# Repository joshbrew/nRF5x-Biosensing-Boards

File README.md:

# nRF52/53 Biosensing Boards

This contains our working prototypes for using nRF52 and nRF53 microcontrollers (ARM + BLE5) with low cost sensors. [Doc](https://docs.google.com/document/d/1gOrWiBDynYziCYDMF4r1Rw85PXo9JbuBrYJEEkW2U-c/edit?usp=sharing). 

License: AGPL v3.0 copyleft (public domain). You may do whatever you want with our designs, but you are obligated to share your modifications and advancements publicly. This is in hopes of facilitating a better community around useful wearable medical hardware designs.

The current prototypes here are working breakout boards. They are pin compatible with several different modules while it's easy to spin up new designs with similar products by Fanstel.

Features Zephyr RTOS test firmware, which is hardware-agnostic. 

### Designs included

- BT40/BT840, pin compatible with any Fanstel BT-series but mind the pinouts as not all will work without modification, but most should.
- BC840M
- BC40M
- BT832A (do not use, this was our first attempt)

### Firmware included

- nRF5340
- nRF52840
- nRF52810 (for the BT832A prototype)

### Sensor Support 
- ADS131M08 (8 channel sigma delta converter), there is one on-board 
- MPU6050 accelerometer
- QMC5883L magnetometer (for 9-axis movement when combined with MPU6050)
- MAX30102 pulse oximeter, 
- BMP/BME280 environmental sensor, 
- Additional 8 channel ADS131M08 for up to 16 raw data channels, each individually configurable. 
- MAX98357A Audio output amplifier
- B079Q8G7N1 PDM MEMS microphone

### [Driver Docs](https://docs.google.com/document/d/1eThhvpdm9zZMaKTB0dwuHXi1aBz_5ESBecHRZPxs0kE/edit?usp=sharing)

You can fairly easily add more sensor modules, which are all plug-and-play so the board can run with any combination of sensors. We'll clean this up more as we go for easier customization and feature inclusions. The BT840/BT40, BC840M, and BC40M prototypes include battery chargers with TVS diodes for safety so the boards could be FDA-approved.

Version 3 (BT40/BT840, BC840M R2 & BC40M R1 designs) by Joshua Brewster and Bojan Jovanovich. Firmware by Bojan Jovanovich, drawings and frontend software by Josh Brewster. 

Versions 2 (BC840M R1) by Joshua Brewster, Jacob Tinkhauser, Bojan Jovanovich. Firmware by Bojan, drawings and frontend software by Josh Brewster. Testing and early design phase included Jacob Tinkhauser. 

Version 0 (BT832A) by Joshua Brewster, Jacob Tinkhauser, and Bojan Jovanovich. Firmware by Bojan and Jacob, drawings and frontend by Joshua Brewster.

Developed for creating open source wearables for biofeedback and treatment recovery monitoring.

Related:
- [BLE & USB Web drivers and debugger](https://github.com/joshbrew/device_debugger)

Below results with the ADS131M08 doing quick tests. Noise floor was around 350 nanovolts when shorted. These are not final results but show lots of promise.

- EEG alpha waves (spikes are blinks through a digital bandpass filter)

- ECG with additional digital 50Hz lowpass

- Raw EOG

- Raw PPG wave (red LED + Photodiode BPW 34 w/ basic 1MOhm + 200pf lowpass filter)

Note the ADS131M08 is pretty much completely useless on USB power as we do not have digital or power isolators. We recommend sticking with the Bluetooth 5 and battery support except for when debugging.

Todos:
- PDFs, but the free EAGLE version works for these simple boards.
- Make the firmware more API-like for adding sensors and easier to cross-compile.
- Upgrade zephyr firmware version to latest Nordic SDK version, need to redo dependencies.
- Finish NFC integration
- Fine tune data throttling

Bug fixing notes:
- Bojan note (old, worked elsewhere): Sensors not booting, build error with the audio settings

Exploratory:
- SD card
- Integration with a graphical device (stay tuned :-))
- Vibration motor integration (just a GPIO on/off)
- Frontend controls for the whole command interface in javascript
- GPS (e.g. LG77L)
- More design modularity, e.g. attachments and hubs

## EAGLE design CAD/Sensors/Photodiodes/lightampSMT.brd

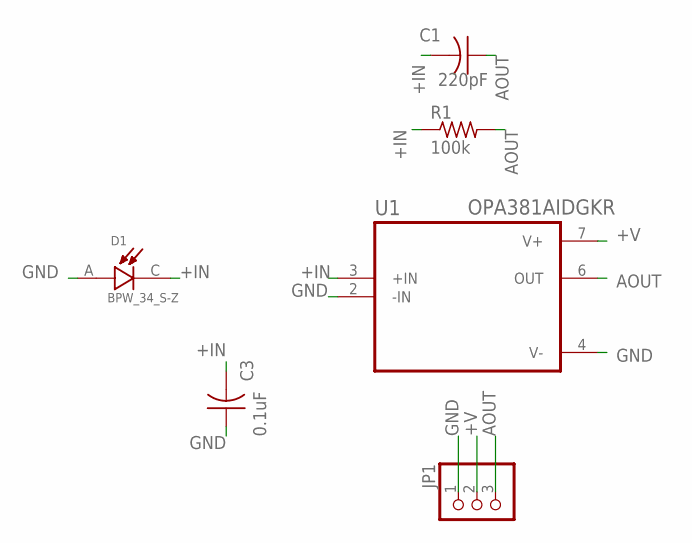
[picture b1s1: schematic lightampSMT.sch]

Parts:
C1: 220pF; C0603K
C3: 0.1uF; C0603K
D1: BPW_34_S-Z; DIO_BPW_34_S-Z
JP1: PINHD-1X3; 1X03
R1: 100k; R0603
U1: OPA381AIDGKR; SOP65P490X110-8N

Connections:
+IN: C1.2, C3.2, D1.C, R1.1, U1.3 (+IN)
+V: JP1.2, U1.7 (V+)
AOUT: C1.1, JP1.3, R1.2, U1.6 (OUT)
GND: C3.1, D1.A, JP1.1, U1.2 (-IN), U1.4 (V-)

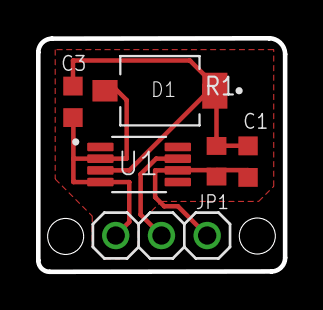
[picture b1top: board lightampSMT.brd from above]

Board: 2 copper layers, 13.7 x 13.0 mm, 6 parts (0 on the bottom side), 4 nets.

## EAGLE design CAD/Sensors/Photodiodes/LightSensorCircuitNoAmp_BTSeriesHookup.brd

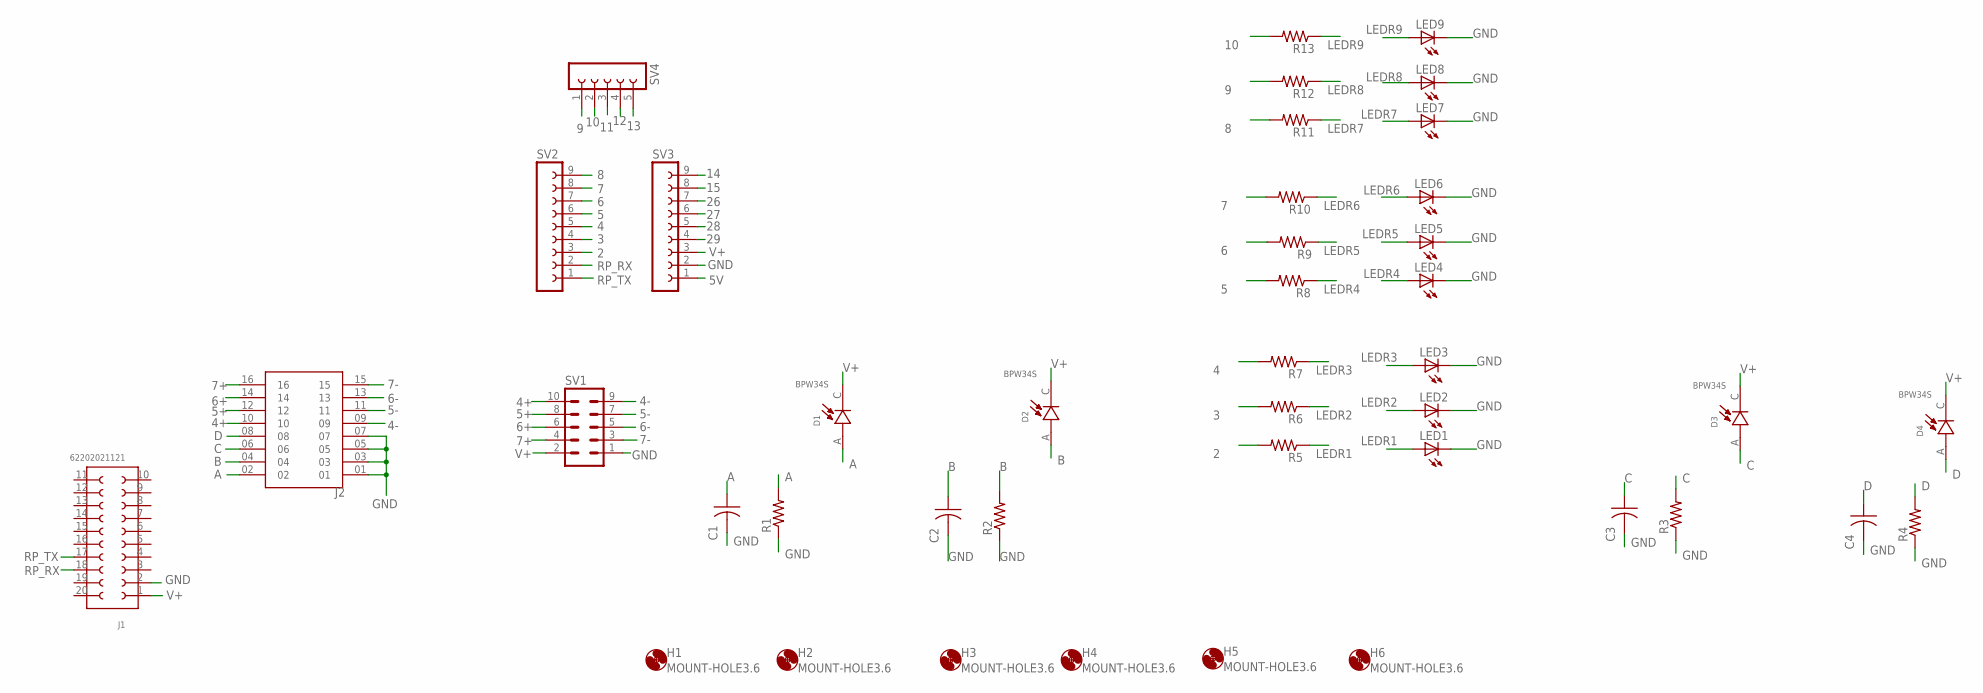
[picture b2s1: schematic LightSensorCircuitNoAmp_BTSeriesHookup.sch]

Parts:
C1, C2, C3, C4: C-US025-025X050; C025-025X050
D1, D2, D3, D4: BPW34S; DIO_BPW34S
H1, H2, H3, H4, H5, H6: MOUNT-HOLE3.6; 3,6
J1: 62202021121
J2: FTSH-108-02-LM-D-ES; SAMTEC_FTSH-108-02-LM-D-ES
LED1, LED2, LED3, LED4, LED5, LED6, LED7, LED8, LED9: LEDCHIPLED_1206; CHIPLED_1206
R1, R2, R3, R4, R5, R6, R7, R8, R9, R10, R11, R12, R13: R-US_0204/5; 0204/5
SV1: MA05-2
SV2, SV3: FE09-1; FE09
SV4: FE05-1

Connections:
2: R5.2, SV2.3
3: R6.2, SV2.4
4: R7.2, SV2.5
4+: J2.10, SV1.10
4-: J2.09, SV1.9
5: R8.2, SV2.6
5+: J2.12, SV1.8
5-: J2.11, SV1.7
5V: SV3.1
6: R9.2, SV2.7
6+: J2.14, SV1.6
6-: J2.13, SV1.5
7: R10.2, SV2.8
7+: J2.16, SV1.4
7-: J2.15, SV1.3
8: R11.2, SV2.9
9: R12.2, SV4.1
10: R13.2, SV4.2
11: SV4.3
12: SV4.4
13: SV4.5
14: SV3.9
15: SV3.8
26: SV3.7
27: SV3.6
28: SV3.5
29: SV3.4
A: C1.1, D1.A, J2.02, R1.2
B: C2.1, D2.A, J2.04, R2.2
C: C3.1, D3.A, J2.06, R3.2
D: C4.1, D4.A, J2.08, R4.2
GND: C1.2, C2.2, C3.2, C4.2, J1.2, J2.01, J2.03, J2.05, J2.07, LED1.C, LED2.C, LED3.C, LED4.C, LED5.C, LED6.C, LED7.C, LED8.C, LED9.C, R1.1, R2.1, R3.1, R4.1, SV1.1, SV3.2
LEDR1: LED1.A, R5.1
LEDR2: LED2.A, R6.1
LEDR3: LED3.A, R7.1
LEDR4: LED4.A, R8.1
LEDR5: LED5.A, R9.1
LEDR6: LED6.A, R10.1
LEDR7: LED7.A, R11.1
LEDR8: LED8.A, R12.1
LEDR9: LED9.A, R13.1
RP_RX: J1.18, SV2.2
RP_TX: J1.17, SV2.1
V+: D1.C, D2.C, D3.C, D4.C, J1.1, SV1.2, SV3.3

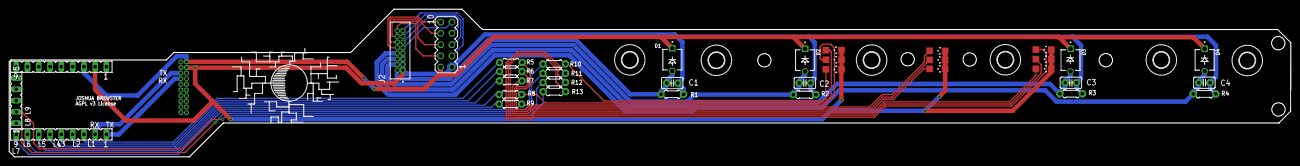
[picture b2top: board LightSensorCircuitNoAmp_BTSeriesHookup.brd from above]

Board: 2 copper layers, 288.6 x 33.2 mm, 42 parts (1 on the bottom side), 34 nets.

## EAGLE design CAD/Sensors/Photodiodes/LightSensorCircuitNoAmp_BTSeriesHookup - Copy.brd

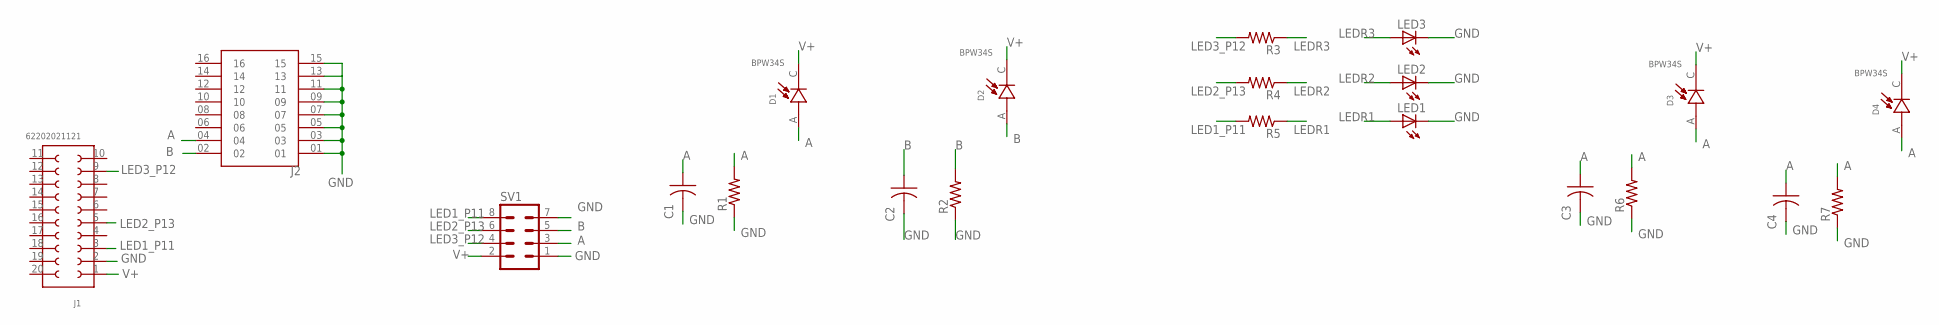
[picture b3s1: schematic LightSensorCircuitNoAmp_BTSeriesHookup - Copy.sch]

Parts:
C1, C2, C3, C4: C-US025-025X050; C025-025X050
D1, D2, D3, D4: BPW34S; DIO_BPW34S
J1: 62202021121
J2: FTSH-108-02-LM-D-ES; SAMTEC_FTSH-108-02-LM-D-ES
LED1, LED2, LED3: LEDCHIPLED_1206; CHIPLED_1206
R1, R2, R3, R4, R5, R6, R7: R-US_0204/5; 0204/5
SV1: MA04-2

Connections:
A: C1.1, C3.1, C4.1, D1.A, D3.A, D4.A, J2.04, R1.2, R6.2, R7.2, SV1.3
B: C2.1, D2.A, J2.02, R2.2, SV1.5
GND: C1.2, C2.2, C3.2, C4.2, J1.2, J2.01, J2.03, J2.05, J2.07, J2.09, J2.11, J2.13, J2.15, LED1.C, LED2.C, LED3.C, R1.1, R2.1, R6.1, R7.1, SV1.1, SV1.7
LED1_P11: J1.3, R5.2, SV1.8
LED2_P13: J1.5, R4.2, SV1.6
LED3_P12: J1.9, R3.2, SV1.4
LEDR1: LED1.A, R5.1
LEDR2: LED2.A, R4.1
LEDR3: LED3.A, R3.1
V+: D1.C, D2.C, D3.C, D4.C, J1.1, SV1.2

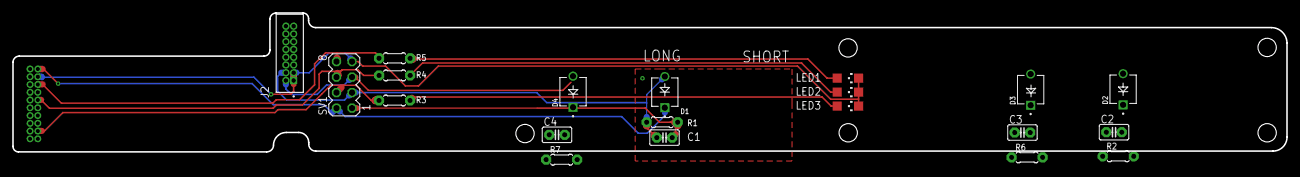
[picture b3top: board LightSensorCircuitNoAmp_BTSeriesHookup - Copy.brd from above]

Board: 2 copper layers, 208.6 x 22.7 mm, 21 parts (1 on the bottom side), 10 nets.

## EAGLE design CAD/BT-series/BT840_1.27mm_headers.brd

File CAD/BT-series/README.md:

Designed for BT840 but compatibile with all Fanstel BT-series microcontrollers (incl BT40 minus the single extra GPIO)

Low cost, minimal size, all 6 mil traces.

Refer to datasheet for BT40 pinout, the board is configured for the BT840 which also has one less pin:

https://www.mouser.com/datasheet/2/915/Fanstel_08262021_BT40F_Product_Specificationsv1_01-2530184.pdf

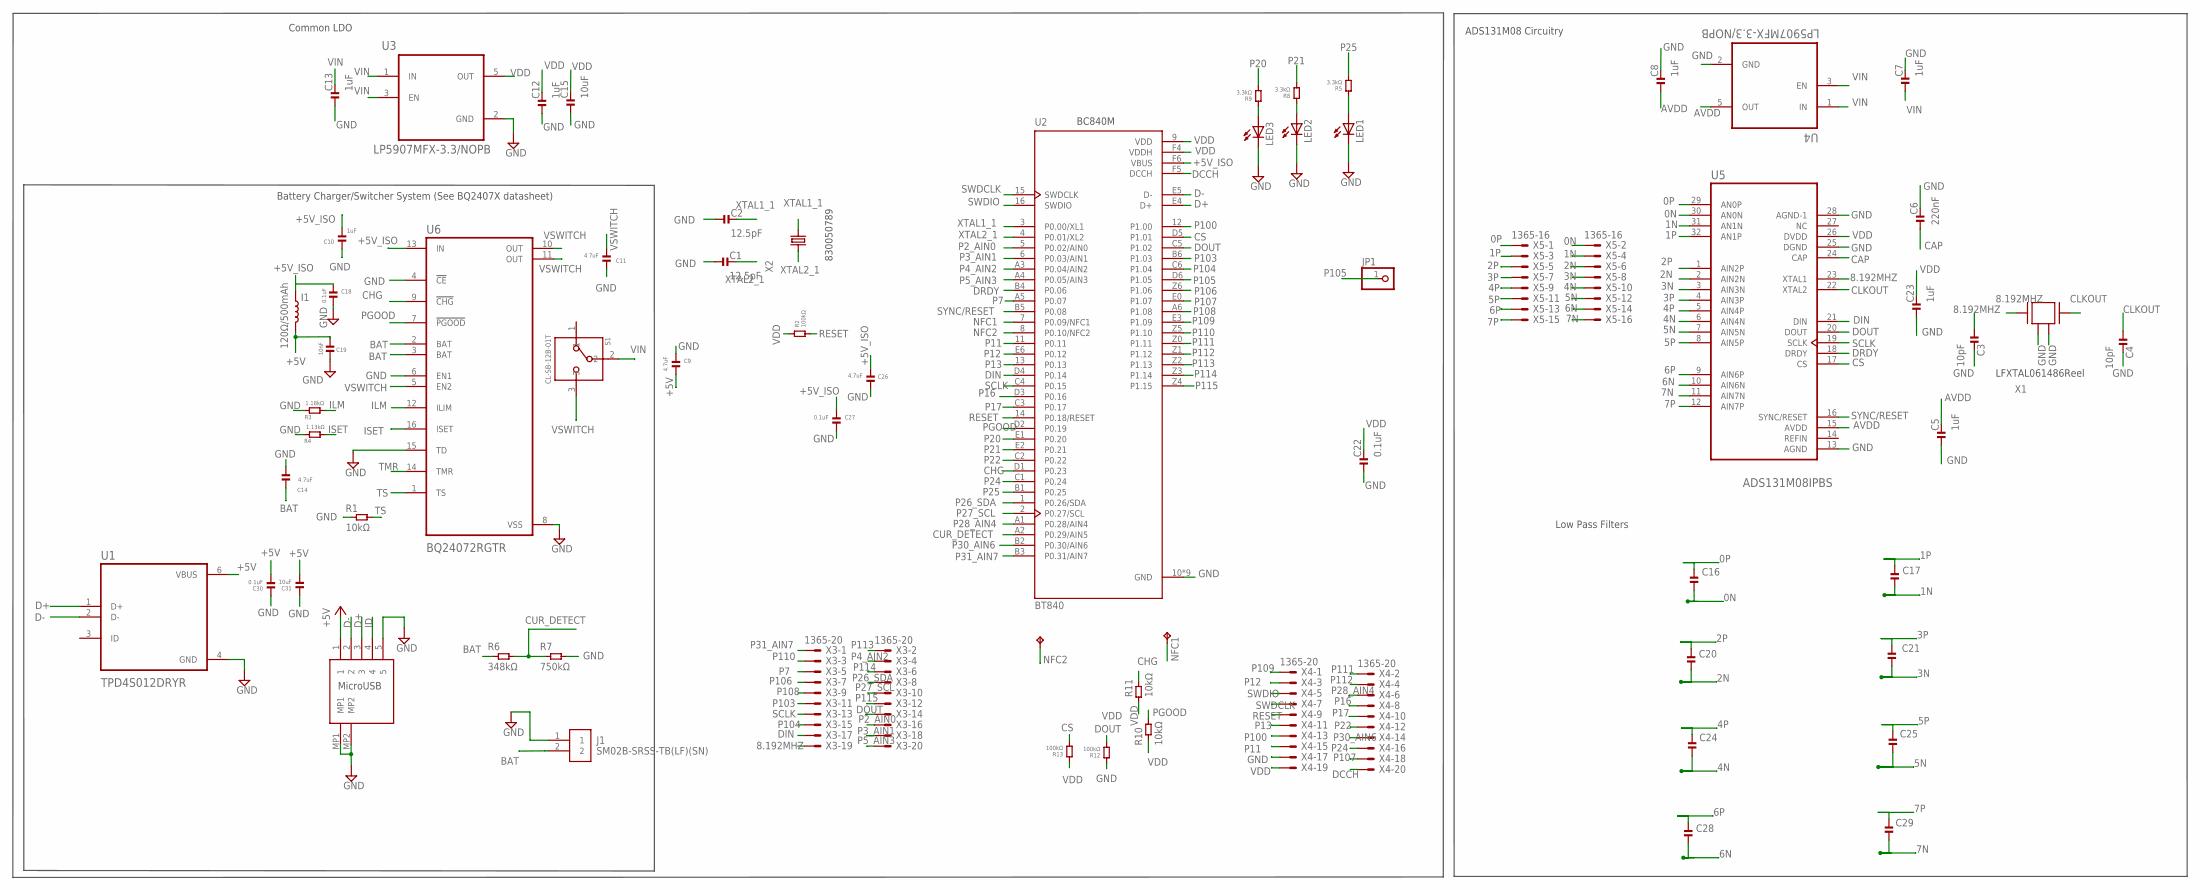
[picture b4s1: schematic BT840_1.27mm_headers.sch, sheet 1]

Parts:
C1, C2: 12.5pF; 0201
C3, C4: 10pF; 0201
C5, C7, C8, C10, C12, C13, C23: 1uF; 0201
C6: 220nF; 0201
C9, C11, C14, C26: 4.7uF; 0201
C15, C31: 10uF; 0402
C16, C17, C20, C21, C24, C25, C28, C29: 100pF; 0201
C18, C22, C27, C30: 0.1uF; 0201
C19: 10nF; 0201
I1: 120Ω/500mAh; 0402_COILCRAFT
J1: SM02B-SRSS-TB(LF)(SN)
JP1: PINHD-1X1; 1X01
LED1, LED2, LED3: LEDCHIPLED_0603; CHIPLED_0603
NFC1, NFC2: TPTP14SQ; TP14SQ
R1: 10kΩ; 0201
R2: 100kΩ; 0201
R3: 1.18kΩ; 0201
R4: 1.13kΩ; 0201
R5, R8, R9: 3.3kΩ; 0201
R6: 348kΩ; 0201
R7: 750kΩ; 0201
R10, R11: 10kΩ; 0402
R12, R13: 100kΩ; 0402
S1: CL-SB-12B-01T; CL-SB-12B
U1: TPD4S012DRYR; PSON50P145X100X60-6N
U2: BT840; XCVR_BT840
U3, U4: LP5907MFX-3.3/NOPB; SOT95P280X145-5N
U5: ADS131M08IPBS; QFP50P700X700X120-32N
U6: BQ24072RGTR; QFN50P300X300X100-17N
U7: DX4R005JJ2R1800
X1: ABM3B-8.000MHZ-B2-T
X2: FC-12M
X3, X4: 1365-20
X5: 1365-16

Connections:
0N: C16.2, U5.30 (AN0N), X5.2
0P: C16.1, U5.29 (AN0P), X5.1
1N: C17.2, U5.31 (AN1N), X5.4
1P: C17.1, U5.32 (AN1P), X5.3
2N: C20.2, U5.2 (AIN2N), X5.6
2P: C20.1, U5.1 (AIN2P), X5.5
3N: C21.2, U5.3 (AIN3N), X5.8
3P: C21.1, U5.4 (AIN3P), X5.7
4N: C24.2, U5.6 (AIN4N), X5.10
4P: C24.1, U5.5 (AIN4P), X5.9
5N: C25.2, U5.7 (AIN5N), X5.12
5P: C25.1, U5.8 (AIN5P), X5.11
6N: C28.2, U5.10 (AIN6N), X5.14
6P: C28.1, U5.9 (AIN6P), X5.13
7N: C29.2, U5.11 (AIN7N), X5.16
7P: C29.1, U5.12 (AIN7P), X5.15
8.192MHZ: C3.1, U5.23 (XTAL1), X1.1, X3.19
+5V: C9.2, C19.2, C30.2, C31.2, I1.P$2 (2), U1.6 (VBUS), U7.1
+5V_ISO: C10.2, C18.1, C26.2, C27.2, I1.P$1 (1), U2.F6 (VBUS), U6.13 (IN)
AVDD: C5.2, C8.1, U4.5 (OUT), U5.15 (AVDD)
BAT: C14.2, J1.2, R6.1, U6.2 (BAT), U6.3 (BAT)
CAP: C6.1, U5.24 (CAP)
CHG: R11.2, U2.D1 (P0.23), U6.9 (!CHG)
CLKOUT: C4.1, U5.22 (XTAL2), X1.3
CS: R13.1, U2.D5 (P1.01), U5.17 (CS)
CUR_DETECT: R6.2, R7.1, U2.A2 (P0.29/AIN5)
D+: U1.1 (D+), U2.E4 (D+), U7.3
D-: U1.2 (D-), U2.E5 (D-), U7.2
DCCH: U2.F5 (DCCH), X4.20
DIN: U2.D4 (P0.14), U5.21 (DIN), X3.17
DOUT: R12.1, U2.C5 (P1.02), U5.20 (DOUT), X3.14
DRDY: U2.B4 (P0.06), U5.18 (DRDY)
GND: C1.1, C2.1, C3.2, C4.2, C5.1, C6.2, C7.2, C8.2, C9.1, C10.1, C11.1, C12.1, C13.1, C14.1, C15.1, C18.2, C19.1, C22.1, C23.1, C26.1, C27.1, C30.1, C31.1, J1.1, LED1.C, LED2.C, LED3.C, R1.1, R3.1, R4.1, R7.2, R12.2, U1.4 (GND), U2.10 (GND), U2.A0 (GND), U2.B0 (GND), U2.C0 (GND), U2.D0 (GND), U2.F0 (GND), U2.F1 (GND), U2.F2 (GND), U2.F3 (GND), U3.2 (GND), U4.2 (GND), U5.13 (AGND), U5.25 (DGND), U5.28 (AGND-1), U6.4 (!CE), U6.6 (EN1), U6.8 (VSS), U6.15 (TD), U7.5, U7.MP1, U7.MP2, X1.2, X1.4, X4.17
ID: U7.4
ILM: R3.2, U6.12 (ILIM)
ISET: R4.2, U6.16 (ISET)
LED1: LED1.A, R5.2
LED2: LED2.A, R8.2
LED3: LED3.A, R9.2
NFC1: NFC2.TP, U2.7 (P0.09/NFC1)
NFC2: NFC1.TP, U2.8 (P0.10/NFC2)
P2_AIN0: U2.5 (P0.02/AIN0), X3.16
P3_AIN1: U2.6 (P0.03/AIN1), X3.18
P4_AIN2: U2.A3 (P0.04/AIN2), X3.4
P5_AIN3: U2.A4 (P0.05/AIN3), X3.20
P7: U2.A5 (P0.07), X3.5
P11: U2.11 (P0.11), X4.15
P12: U2.E6 (P0.12), X4.3
P13: U2.13 (P0.13), X4.11
P16: U2.D3 (P0.16), X4.8
P17: U2.C3 (P0.17), X4.10
P20: R9.1, U2.E1 (P0.20)
P21: R8.1, U2.E2 (P0.21)
P22: U2.C2 (P0.22), X4.12
P24: U2.C1 (P0.24), X4.16
P25: R5.1, U2.B1 (P0.25)
P26_SDA: U2.1 (P0.26/SDA), X3.8
P27_SCL: U2.2 (P0.27/SCL), X3.10
P28_AIN4: U2.A1 (P0.28/AIN4), X4.6
P30_AIN6: U2.B2 (P0.30/AIN6), X4.14
P31_AIN7: U2.B3 (P0.31/AIN7), X3.1
P100: U2.12 (P1.00), X4.13
P103: U2.B6 (P1.03), X3.11
P104: U2.C6 (P1.04), X3.15
P105: JP1.1, U2.D6 (P1.05)
P106: U2.Z6 (P1.06), X3.7
P107: U2.E0 (P1.07), X4.18
P108: U2.A6 (P1.08), X3.9
P109: U2.E3 (P1.09), X4.1
P110: U2.Z5 (P1.10), X3.3
P111: U2.Z0 (P1.11), X4.2
P112: U2.Z1 (P1.12), X4.4
P113: U2.Z2 (P1.13), X3.2
P114: U2.Z3 (P1.14), X3.6
P115: U2.Z4 (P1.15), X3.12
PGOOD: R10.2, U2.D2 (P0.19), U6.7 (!PGOOD)
RESET: R2.1, U2.14 (P0.18/RESET), X4.9
SCLK: U2.C4 (P0.15), U5.19 (SCLK), X3.13
SWDCLK: U2.15 (SWDCLK), X4.7
SWDIO: U2.16 (SWDIO), X4.5
SYNC/RESET: U2.B5 (P0.08), U5.16 (SYNC/RESET)
TMR: U6.14 (TMR)
TS: R1.2, U6.1 (TS)
VDD: C12.2, C15.2, C22.2, C23.2, R2.2, R10.1, R11.1, R13.2, U2.9 (VDD), U2.F4 (VDDH), U3.5 (OUT), U5.26 (DVDD), X4.19
VIN: C7.1, C13.2, S1.2, U3.1 (IN), U3.3 (EN), U4.1 (IN), U4.3 (EN)
VSWITCH: C11.2, S1.3, U6.5 (EN2), U6.10 (OUT), U6.11 (OUT)
XTAL1_1: C2.2, U2.3 (P0.00/XL1), X2.2
XTAL2_1: C1.2, U2.4 (P0.01/XL2), X2.1

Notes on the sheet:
LFXTAL061486Reel
830050789
MicroUSB
Battery Charger/Switcher System (See BQ2407X datasheet)
ADS131M08 Circuitry
Common LDO
BC840M
Low Pass Filters

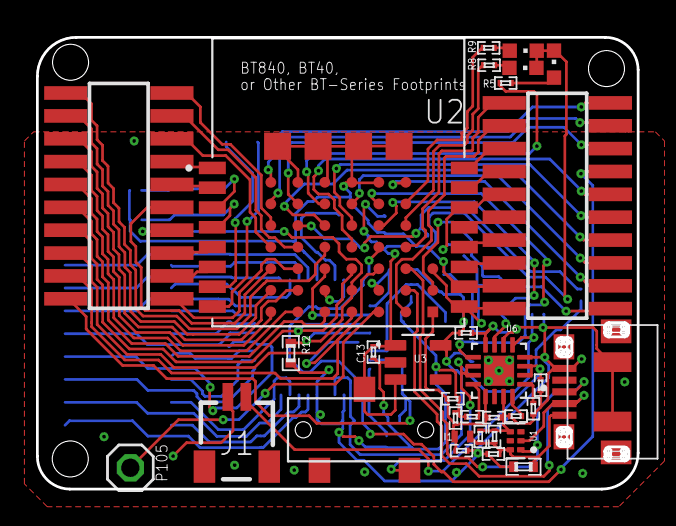
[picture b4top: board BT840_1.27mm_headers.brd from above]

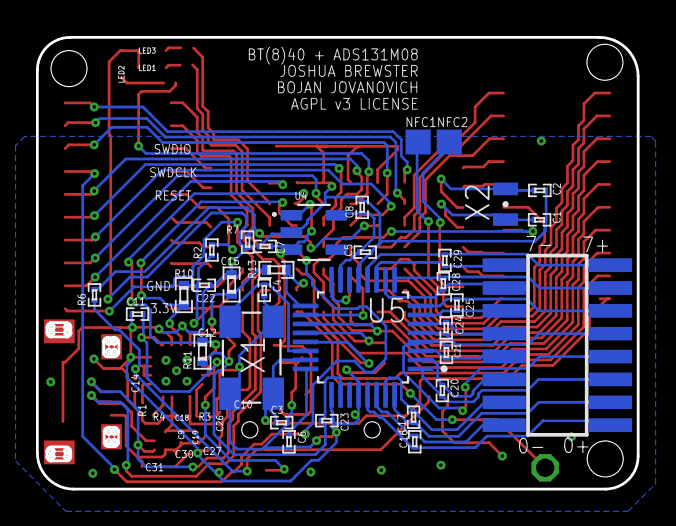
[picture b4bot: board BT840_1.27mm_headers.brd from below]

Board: 2 copper layers, 33.4 x 25.1 mm, 65 parts (33 on the bottom side), 86 nets.

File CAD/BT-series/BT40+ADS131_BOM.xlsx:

Designators | Ct | Part # | Description | Substitutes | NOTES | Costs (old) | 1.0 | 10.0 | 100.0 | 1000.0
U1 | 1.0 | TPD4S012DRYR | TVS Diodes |  |  |  | 0.73 | 6.48 | 49.7 | 314.0
U2 | 1.0 | BT40 | Fanstel Microcontroller | BT840, BT832, BT832A, or variants (F, E, X, XE) | Prefer BT40 (nRF53) | From Fanstel: | 10.41 | 99.8 | 998.0 | 7650.0
U3,U4 | 2.0 | LP5907-3.3MFX | 3v3 LDO | Alt Stock (moq 155) |  |  | 0.7 | 5.93 | 41.1 | 269.0
U5 | 1.0 | ADS131M08IPBS | ADC 24bit 8ch |  |  | From TI: | 7.739 | 77.39 | 630.9 | 4206
U6 | 1.0 | BQ24076RGTR | Battery charge/switch interface | BQ2407xRGTR |  |  | 2.52 | 22.7 | 183.0 | 1250.0
U7 | 1.0 | DX4R005JJ2R1800 | MicroUSB port |  |  |  | 0.79 | 6.32 | 54.9 | 386.0
S1 | 1.0 | CL-SB-12B-01T | Switch On-Off | Alt part/source |  |  | 0.93 | 8.37 | 66.1 | 533.0
X1 | 1.0 | LFXTAL061486Reel | 8.192Mhz Crystal |  |  |  | 0.92 | 7.63 | 67.5 | 516.0
X2 | 1.0 | 8.30105946101E11 | 32.7680 Crystal |  |  |  | 0.67 | 6.11 | 52.4 | 524
I1 | 1.0 | MMZ1005S121CT000 | 120Ohm/500mAh 0402 INDUCTOR |  |  |  | 0.1 | 0.54 | 2.9 | 23.0
C1,C2 | 2.0 | CC0201DRNPO9BN7R0 | 7pF 0201 MLCC |  |  |  | 0.2 | 0.37 | 1.8 | 10.0
C3,C4, | 2.0 | 02015A100JAT2A | 10pF 0201 MLCC |  |  |  | 0.2 | 0.37 | 1.8 | 10.0
C5,C7,C8,C10,C12,C13,C23 | 7.0 | 02016D224KAT2A | 1uF 0201 MLCC |  |  |  | 0.7 | 0.37 | 1.8 | 10.0
C6 | 1.0 | 02016D224KAT2A | 220nF 0201 MLCC |  |  |  | 0.1 | 0.37 | 1.8 | 10.0
C9,C11,C14,C26 | 4.0 | AMK063EBJ475MP-F | 4.7uF 0201 MLCC |  |  |  | 0.4 | 1.48 | 7.2 | 40
C15,C31 | 2.0 | 0402YG104ZAT4A | 10uF 0402 MLCC |  |  |  | 0.2 | 0.74 | 3.6 | 20
C18,C22,C27,C30 | 4.0 | 0201ZD104KAT2A | 0.1uF 0201 MLCC |  |  |  | 0.4 | 1.48 | 7.2 | 40
C19 | 1.0 | 0201YD103KAT4A | 10nF 0201 MLCC |  |  |  | 0.8 | 2.96 | 14.4 | 80
C16,C17,C20,C21,C24,C25,C28,C29 | 8.0 | 02013C101KAT2A | 100pF 0201 MLCC |  |  |  | 0.1 | 0.37 | 1.8 | 10.0
R1 | 1.0 | CRCW020110K0JNED | 10KOhm 0201 RESISTOR |  |  |  | 0.2 | 0.2 | 4.8 | 8.0
R10, R11 | 2.0 | AC0402FR-0710KL | 10KOhm 0402 RESISTOR |  |  |  | 0.1 | 0.2 | 4.8 | 8.0
R2 | 1.0 | CRCW0201100KFNED | 100KOhm 0201 RESISTOR |  |  |  | 0.1 | 0.2 | 4.8 | 8.0
R12,R13 | 2.0 | AC0402FR-13100KL | 100KOhm 0402 RESISTOR |  |  |  | 0.1 | 0.2 | 4.8 | 8.0
R6 | 1.0 | RC0201FR-07348KL | 348KOhm 0201 RESISTOR |  |  |  | 0.1 | 0.2 | 4.8 | 8.0
R7 | 1.0 | RC0201FR-07750KL | 750KOhm 0201 RESISTOR |  |  |  | 0.1 | 0.2 | 4.8 | 8.0
R5,R8,R9 | 3.0 | RC0201FR-073K3L | 3.3KOhm 0201 RESISTOR |  |  |  | 0.1 | 0.2 | 4.8 | 8.0
R3 | 1.0 | RC0201FR-071K18L | 1.18KOhm 0201 RESISTOR |  |  |  | 0.1 | 0.2 | 4.8 | 8.0
R4 | 1.0 | ERJ-1GNF1131C | 1.13KOhm 0201 RESISTOR |  |  |  | 0.1 | 0.2 | 4.8 | 8.0
JP1 | 1.0 | NPTC082KFMS-RC | 2X8 SMT 1.25MM HEADER FEMALE |  |  |  | 1.89 | 16.41 | 146.66 | 1047.6
JP2,JP3 | 2.0 | NPTC102KFMS-RC | 2X10 SMT 1.25MM HEADER FEMALE
LED1 | 1.0 | AA1608SESK | 0603 CHIPLED ORANGE |  |  |  | 0.48 | 2.81 | 16.2 | 127.0
LED2 | 1.0 | AA1608QBS/D-10MAV | 0603 CHIPLED BLUE |  |  |  | 0.48 | 2.81 | 16.2 | 127.0
LED3 | 1.0 | AA1608ZGSK-10MAV | 0603 CHIPLED GREEN |  |  |  | 0.46 | 2.96 | 22.8 | 151.0
J1 | 1.0 | SM02B-SRSS-TB(LF)(SN) | CONN HEADER SH 2POS 1MM
total | 62 |  |  |  |  |  | 32.919 | 276.57 | 2432.96 | 17425.6
 |  |  | CONN HOUSING JST-SH 2POS 1MM | Stock? or Stock? |  | Unit Cost | 32.919 | 27.657 | 24.3296 | 17.4256
 |  |  |  |  |  | Does not include battery, and peripherals
 |  |  |  |  |  | W/out headers | 31.029 | 260.16 | 2286.3 | 16378
 |  |  |  |  |  | Unit Cost | 31.029 | 26.016 | 22.863 | 16.378
 |  |  |  |  |  | Unit cost w/ Battery, figure $2.50 per | 35.419 | 30.157 | 26.8296 | 19.9256
 |  |  |  |  |  | Add Peripherals, ~$9 off Aliexpress | 44.419 | 39.157 | 35.8296 | 28.9256
 |  |  |  |  |  | Add PCBWay PCBs | 48.419 | 43.157 | 36.9596 | 29.3256 | Cost for 200 boards: 226. Minimum 10, board cost for 1000 estimated from online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
 |  |  |  |  |  | Add Portland assembly cost (lowest) | 270.889 | 154.392 | 67.0296 | 50.2856 | 5 minimum
 |  |  |  |  |  | Add the plastic band and flex connector?

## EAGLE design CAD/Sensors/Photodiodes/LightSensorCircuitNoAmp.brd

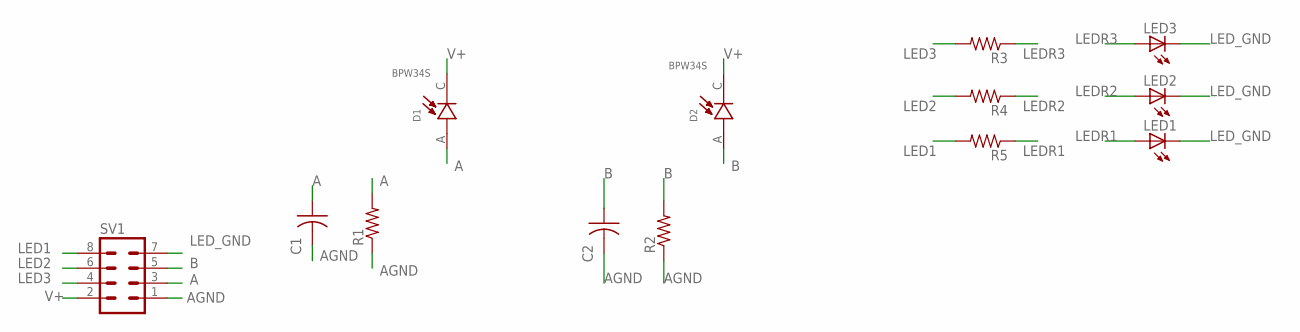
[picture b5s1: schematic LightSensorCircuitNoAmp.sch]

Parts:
C1, C2: C-US025-025X050; C025-025X050
D1, D2: BPW34S; DIO_BPW34S
LED1, LED2, LED3: LEDCHIPLED_1206; CHIPLED_1206
R1, R2, R3, R4, R5: R-US_0204/5; 0204/5
SV1: MA04-2

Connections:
A: C1.1, D1.A, R1.2, SV1.3
AGND: C1.2, C2.2, R1.1, R2.1, SV1.1
B: C2.1, D2.A, R2.2, SV1.5
LED1: R5.2, SV1.8
LED2: R4.2, SV1.6
LED3: R3.2, SV1.4
LEDR1: LED1.A, R5.1
LEDR2: LED2.A, R4.1
LEDR3: LED3.A, R3.1
LED_GND: LED1.C, LED2.C, LED3.C, SV1.7
V+: D1.C, D2.C, SV1.2

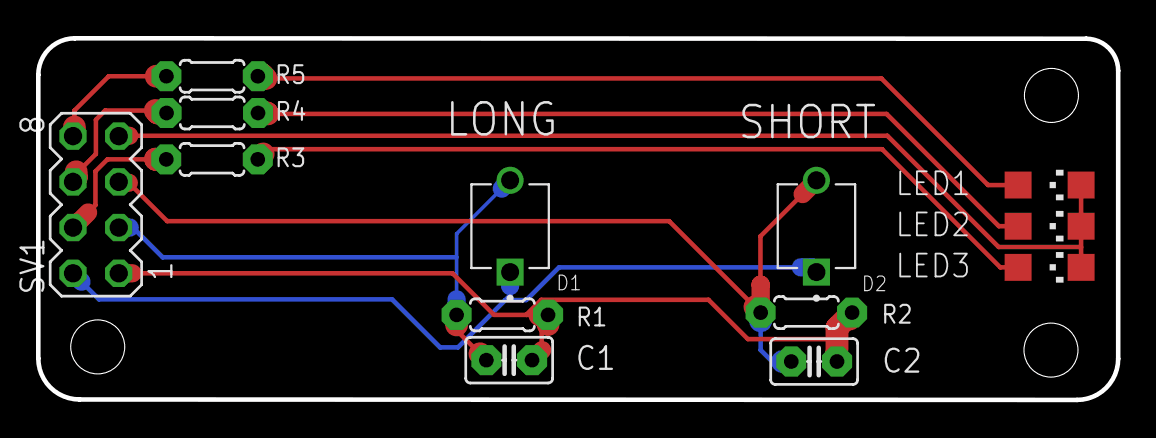
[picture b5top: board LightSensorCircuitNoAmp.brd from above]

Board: 2 copper layers, 60.0 x 20.1 mm, 13 parts (0 on the bottom side), 11 nets.

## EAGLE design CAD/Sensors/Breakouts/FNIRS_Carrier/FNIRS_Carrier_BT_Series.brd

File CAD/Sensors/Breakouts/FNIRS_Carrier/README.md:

- Use the BT-series boards. The pinouts are defined for the BT840 specifically.

- ADS131M08 breakout for 8+ more channels at https://github.com/joshbrew/ADS131M08_Arduino
- FNIRS carrier board for DIY_DOT project.
- See the DOT Headset boards at at https://github.com/joshbrew/DIY_DOT

- MAX30102 breakout and the unfinished biosensing shield breakout by Arthur Jordan

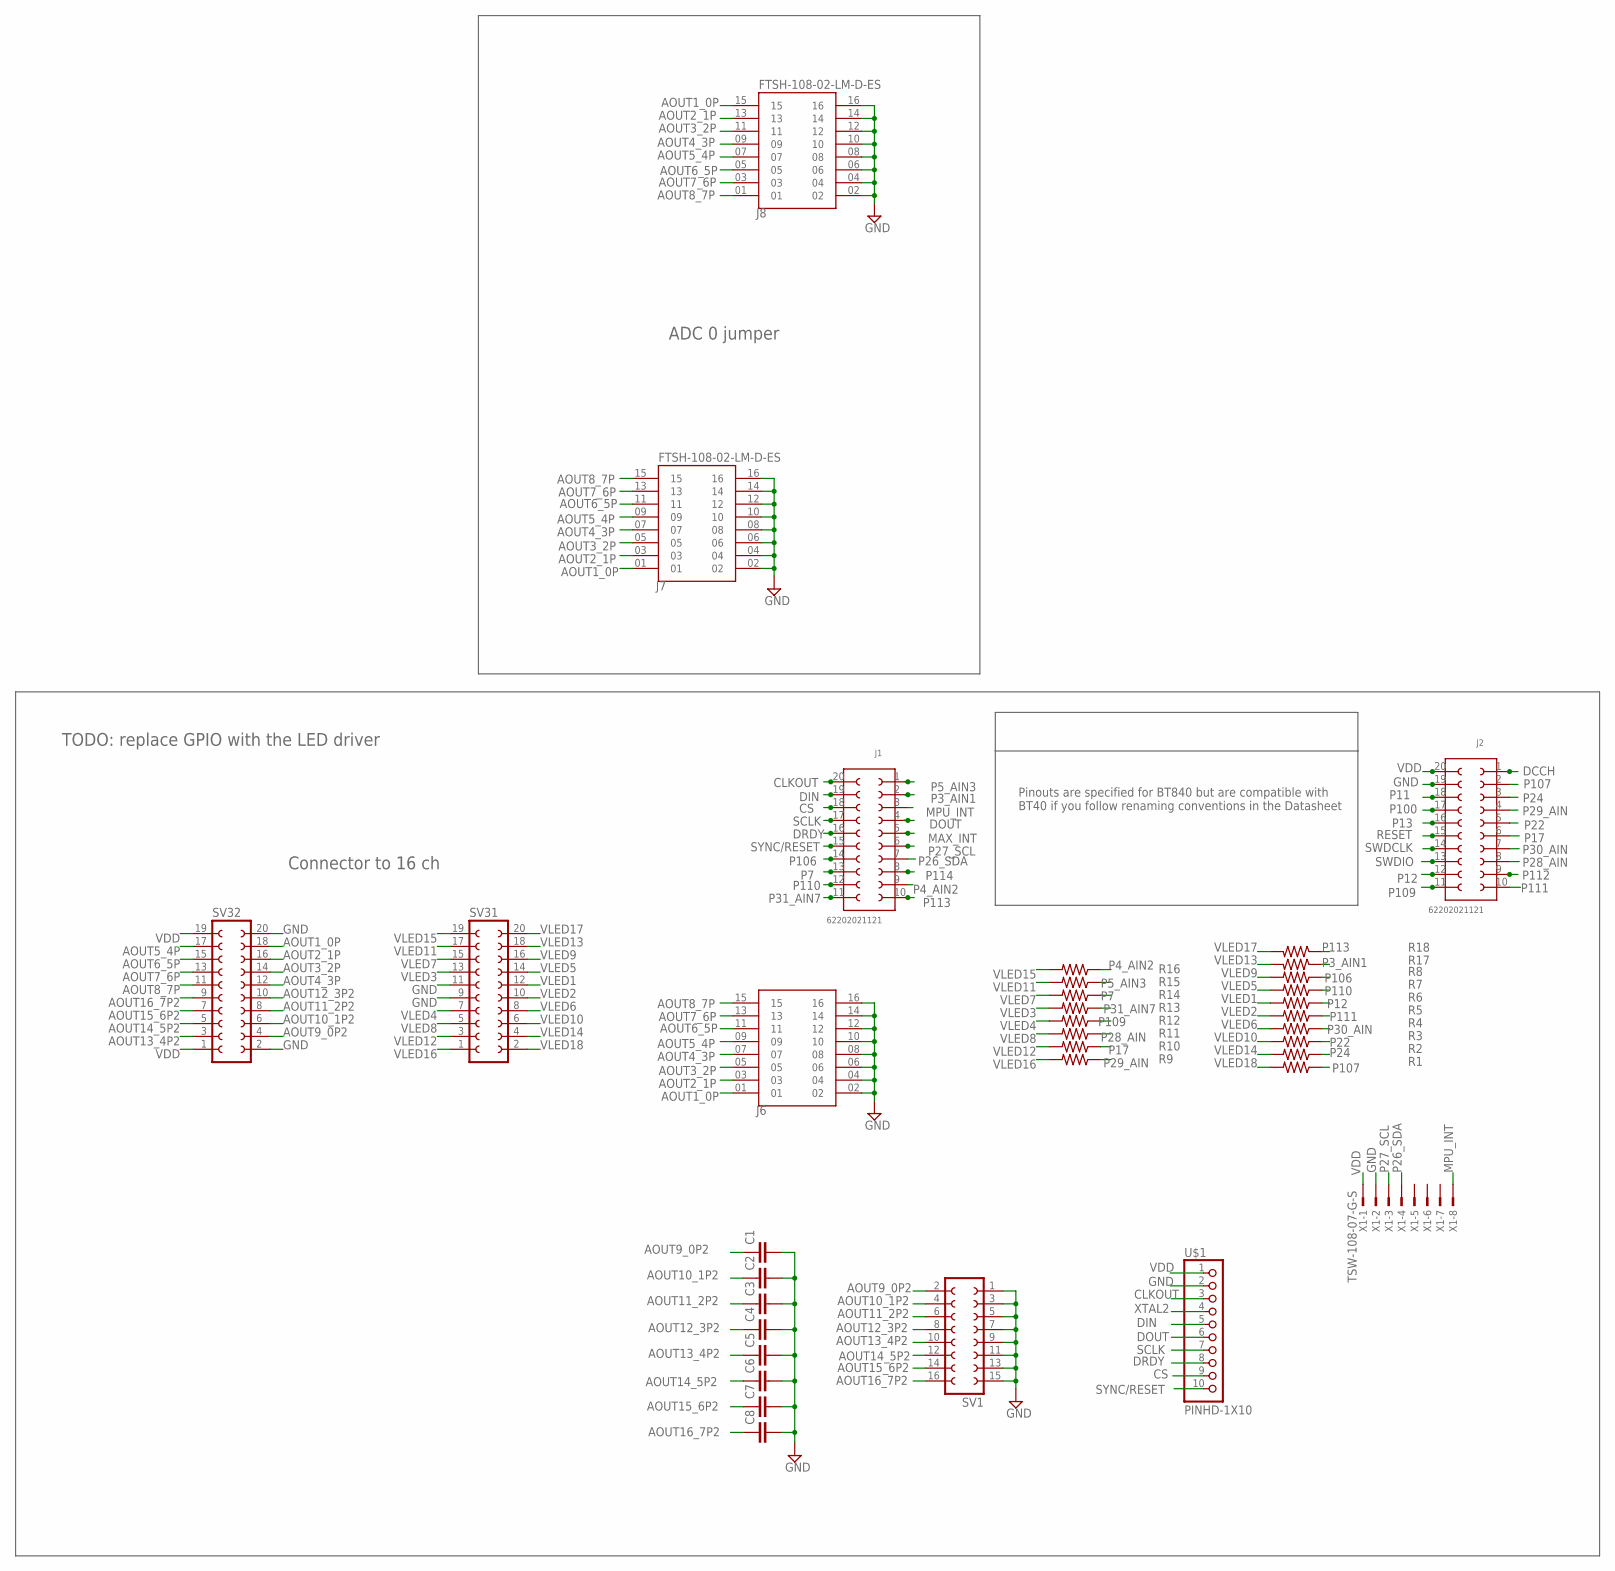
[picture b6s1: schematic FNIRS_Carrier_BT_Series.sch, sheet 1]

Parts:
C1, C2, C3, C4, C5, C6, C7, C8: C2.5/2; C2.5-2
J1, J2: 62202021121
J6, J7, J8: FTSH-108-02-LM-D-ES; SAMTEC_FTSH-108-02-LM-D-ES
R1, R2, R3, R4, R5, R6, R7, R8, R9, R10, R11, R12, R13, R14, R15, R16, R17, R18: R-US_0204/5; 0204/5
SV1: FE08-2
SV31, SV32: FE10-2
U$1: PINHD-1X10; 1X10-BIG
X1: TSW-108-07-G-S; TSW-108-XX-G-S

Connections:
AOUT1_0P: J6.01, J7.01, J8.15, SV32.18
AOUT2_1P: J6.03, J7.03, J8.13, SV32.16
AOUT3_2P: J6.05, J7.05, J8.11, SV32.14
AOUT4_3P: J6.07, J7.07, J8.09, SV32.12
AOUT5_4P: J6.09, J7.09, J8.07, SV32.17
AOUT6_5P: J6.11, J7.11, J8.05, SV32.15
AOUT7_6P: J6.13, J7.13, J8.03, SV32.13
AOUT8_7P: J6.15, J7.15, J8.01, SV32.11
AOUT9_0P2: C1.1, SV1.2, SV32.4
AOUT10_1P2: C2.1, SV1.4, SV32.6
AOUT11_2P2: C3.1, SV1.6, SV32.8
AOUT12_3P2: C4.1, SV1.8, SV32.10
AOUT13_4P2: C5.1, SV1.10, SV32.3
AOUT14_5P2: C6.1, SV1.12, SV32.5
AOUT15_6P2: C7.1, SV1.14, SV32.7
AOUT16_7P2: C8.1, SV1.16, SV32.9
CLKOUT: J1.20, U$1.3
CS: J1.18, U$1.9
DCCH: J2.1
DIN: J1.19, U$1.5
DOUT: J1.4, U$1.6
DRDY: J1.16, U$1.8
GND: C1.2, C2.2, C3.2, C4.2, C5.2, C6.2, C7.2, C8.2, J2.19, J6.02, J6.04, J6.06, J6.08, J6.10, J6.12, J6.14, J6.16, J7.02, J7.04, J7.06, J7.08, J7.10, J7.12, J7.14, J7.16, J8.02, J8.04, J8.06, J8.08, J8.10, J8.12, J8.14, J8.16, SV1.1, SV1.3, SV1.5, SV1.7, SV1.9, SV1.11, SV1.13, SV1.15, SV31.9, SV31.11, SV32.2, SV32.20, U$1.2, X1.2
MAX_INT: J1.5
MPU_INT: J1.3, X1.8
P3_AIN1: J1.2, R17.1
P4_AIN2: J1.9, R16.1
P5_AIN3: J1.1, R15.1
P7: J1.13, R14.1
P11: J2.18
P12: J2.12, R6.1
P13: J2.16
P17: J2.6, R10.1
P22: J2.5, R3.1
P24: J2.3, R2.1
P26_SDA: J1.7, X1.4
P27_SCL: J1.6, X1.3
P28_AIN: J2.8, R11.1
P29_AIN: J2.4, R9.1
P30_AIN: J2.7, R4.1
P31_AIN7: J1.11, R13.1
P100: J2.17
P106: J1.14, R8.1
P107: J2.2, R1.1
P109: J2.11, R12.1
P110: J1.12, R7.1
P111: J2.10, R5.1
P112: J2.9
P113: J1.10, R18.1
P114: J1.8
RESET: J2.15
SCLK: J1.17, U$1.7
SWDCLK: J2.14
SWDIO: J2.13
SYNC/RESET: J1.15, U$1.10
VDD: J2.20, SV32.1, SV32.19, U$1.1, X1.1
VLED1: R6.2, SV31.12
VLED2: R5.2, SV31.10
VLED3: R13.2, SV31.13
VLED4: R12.2, SV31.7
VLED5: R7.2, SV31.14
VLED6: R4.2, SV31.8
VLED7: R14.2, SV31.15
VLED8: R11.2, SV31.5
VLED9: R8.2, SV31.16
VLED10: R3.2, SV31.6
VLED11: R15.2, SV31.17
VLED12: R10.2, SV31.3
VLED13: R17.2, SV31.18
VLED14: R2.2, SV31.4
VLED15: R16.2, SV31.19
VLED16: R9.2, SV31.1
VLED17: R18.2, SV31.20
VLED18: R1.2, SV31.2
XTAL2: U$1.4

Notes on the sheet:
Pinouts are specified for BT840 but are compatible with BT40 if you follow renaming conventions in the Datasheet
ADC 0 jumper
Connector to 16 ch
TODO: replace GPIO with the LED driver

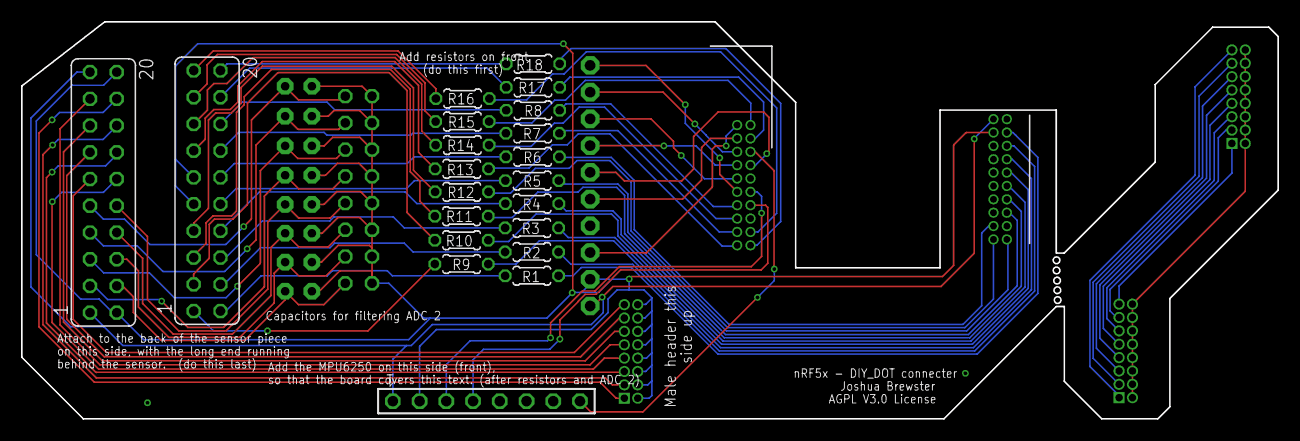
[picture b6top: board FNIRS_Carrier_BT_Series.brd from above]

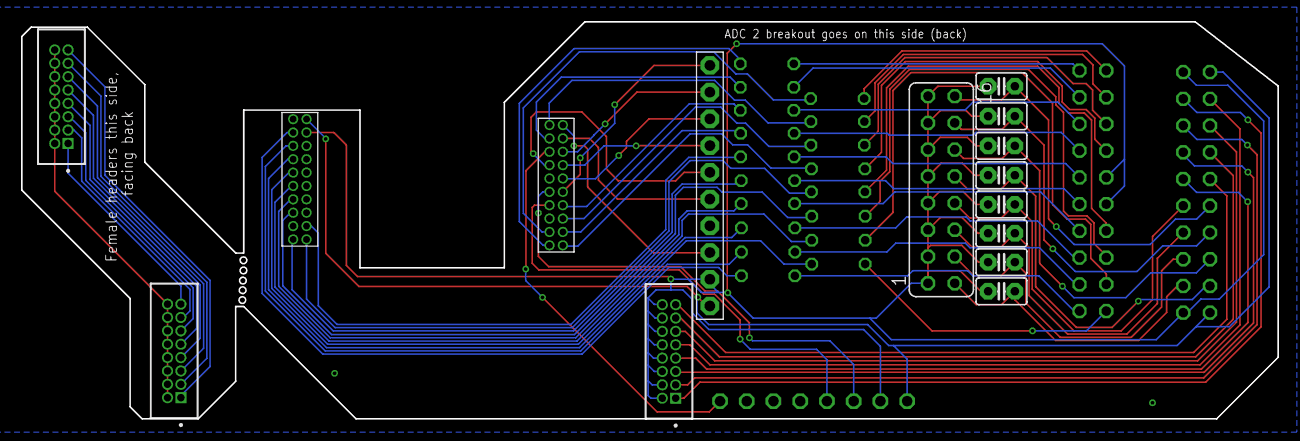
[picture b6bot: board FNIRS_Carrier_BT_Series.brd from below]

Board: 2 copper layers, 119.4 x 37.7 mm, 36 parts (15 on the bottom side), 64 nets.

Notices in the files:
CAD/BT-series/BT840_1.27mm_headers.brd:
AGPL v3 LICENSE
CAD/Sensors/Breakouts/FNIRS_Carrier/FNIRS_Carrier_BT_Series.brd:
AGPL V3.0 License
parts and their libraries:
spkfncoils: Licensing: Creative Commons ShareAlike 4.0 International - https://creativecommons.org/licenses/by-sa/4.0
COPYRIGHT: Copyright (C) 2022 Ultra Librarian. All rights reserved.
